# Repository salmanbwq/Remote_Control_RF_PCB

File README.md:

# Remote_Control_RF_PCB
## Decripción
En este repositorio se encuentra el diseño de la placa del Control remoto RF/IR/RFID

Los diseños han sido creador a mano y algunos sacados de https://www.snapeda.com/ y https://4dsystems.com.au/

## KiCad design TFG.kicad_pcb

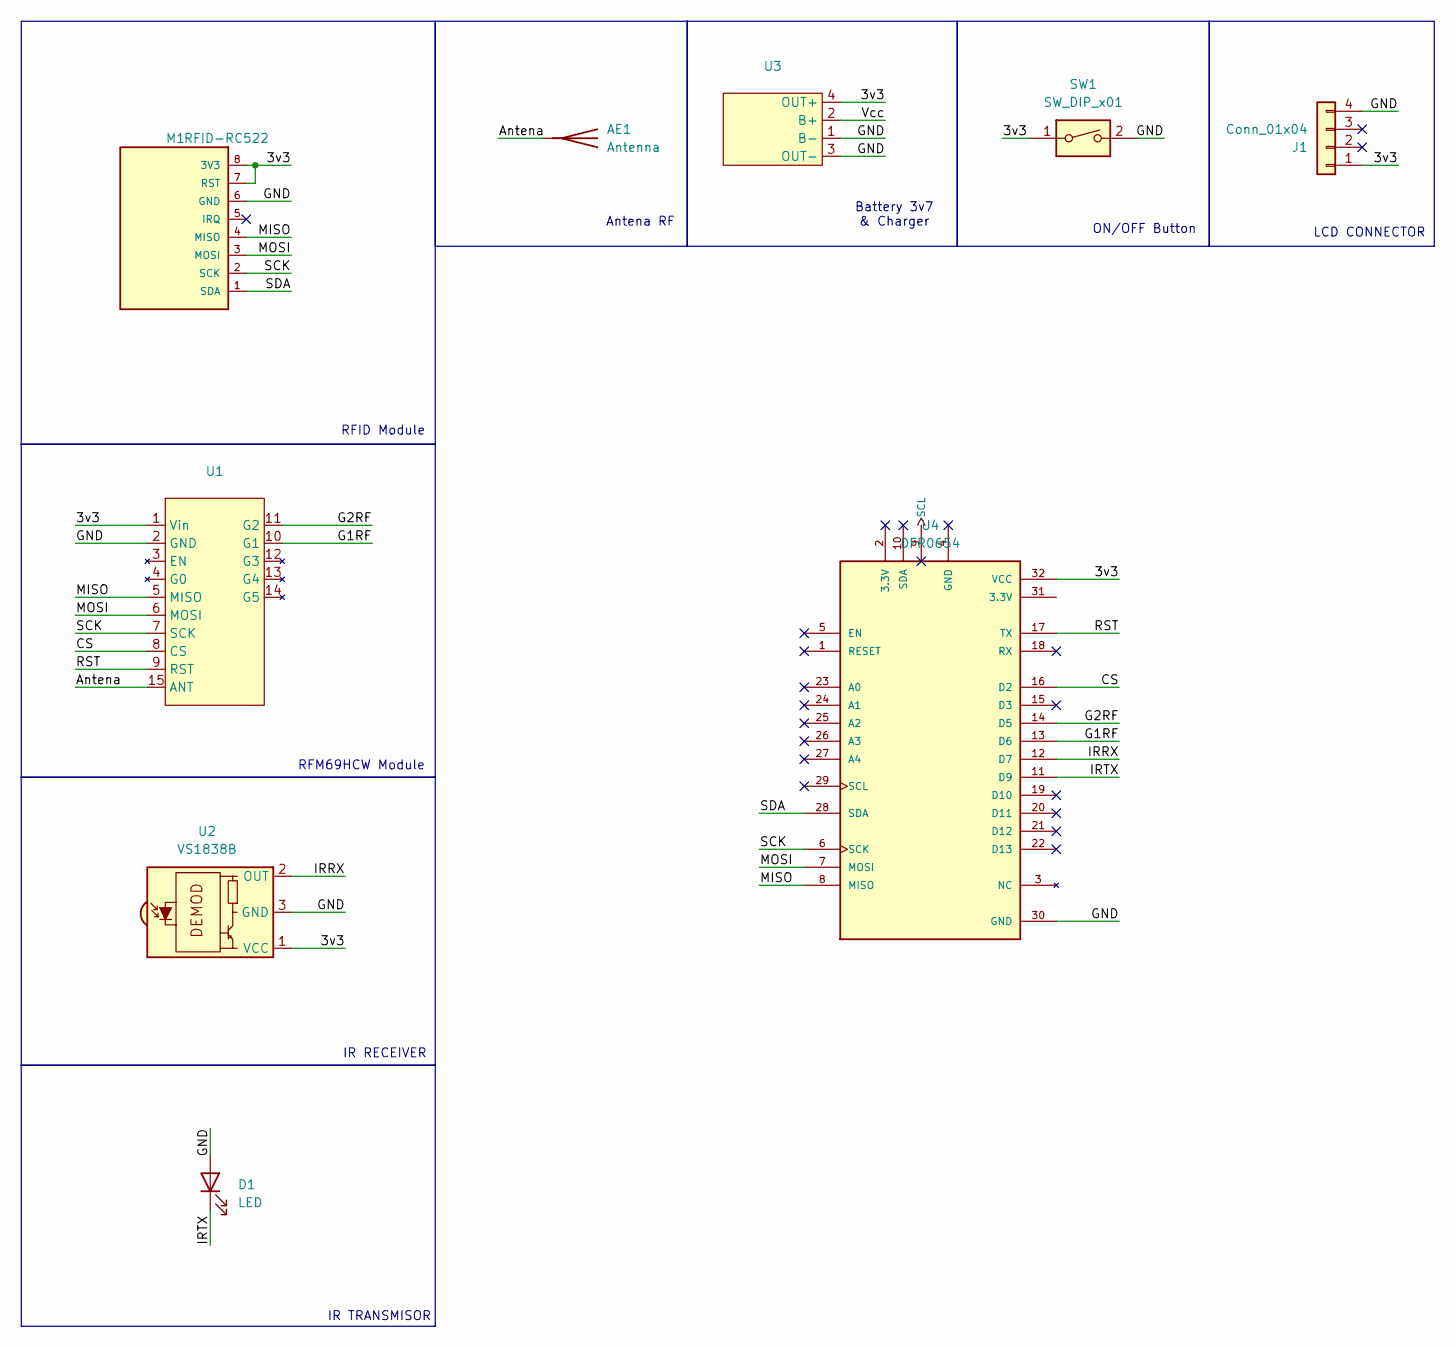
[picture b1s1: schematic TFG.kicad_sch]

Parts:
AE1: Antenna; PinHeader_1x01_P2.54mm_Vertical
D1: LED; LED_D3.0mm_Horizontal_O1.27mm_Z2.0mm_IRBlack
J1: Conn_01x04; JST_EH_B4B-EH-A_1x04_P2.50mm_Vertical
M1: RFID-RC522; MPN RFID-RC522
SW1: SW_DIP_x01; PinSocket_1x02_P2.54mm_Vertical
U1: RF69HCW
U2: VS1838B; Vishay_CAST-3Pin
U3: Battery charger
U4: DFR0654; MODULE_DFR0654

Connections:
/3v3: J1.1, M1.7 (RST), M1.8 (3V3), SW1.1, U1.1 (Vin), U2.1 (VCC), U3.4 (OUT+), U4.32 (VCC)
/Antena: AE1.1 (A), U1.15 (ANT)
/CS: U1.8 (CS), U4.16 (D2)
/G1RF: U1.10 (G1), U4.13 (D6)
/G2RF: U1.11 (G2), U4.14 (D5)
/GND: D1.2 (A), J1.4, M1.6 (GND), SW1.2, U1.2 (GND), U2.3 (GND), U3.1 (B-), U3.3 (OUT-), U4.30 (GND)
/IRRX: U2.2 (OUT), U4.12 (D7)
/IRTX: D1.1 (K), U4.11 (D9)
/MISO: M1.4 (MISO), U1.5 (MISO), U4.8 (MISO)
/MOSI: M1.3 (MOSI), U1.6 (MOSI), U4.7 (MOSI)
/RST: U1.9 (RST), U4.17 (TX)
/SCK: M1.2 (SCK), U1.7 (SCK), U4.6 (SCK)
/SDA: M1.1 (SDA), U4.28 (SDA)
/Vcc: U3.2 (B+)

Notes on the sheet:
IR RECEIVER
RFM69HCW Module
IR TRANSMISOR
RFID Module
LCD CONNECTOR
Antena RF
ON/OFF Button
Battery 3v7 & Charger

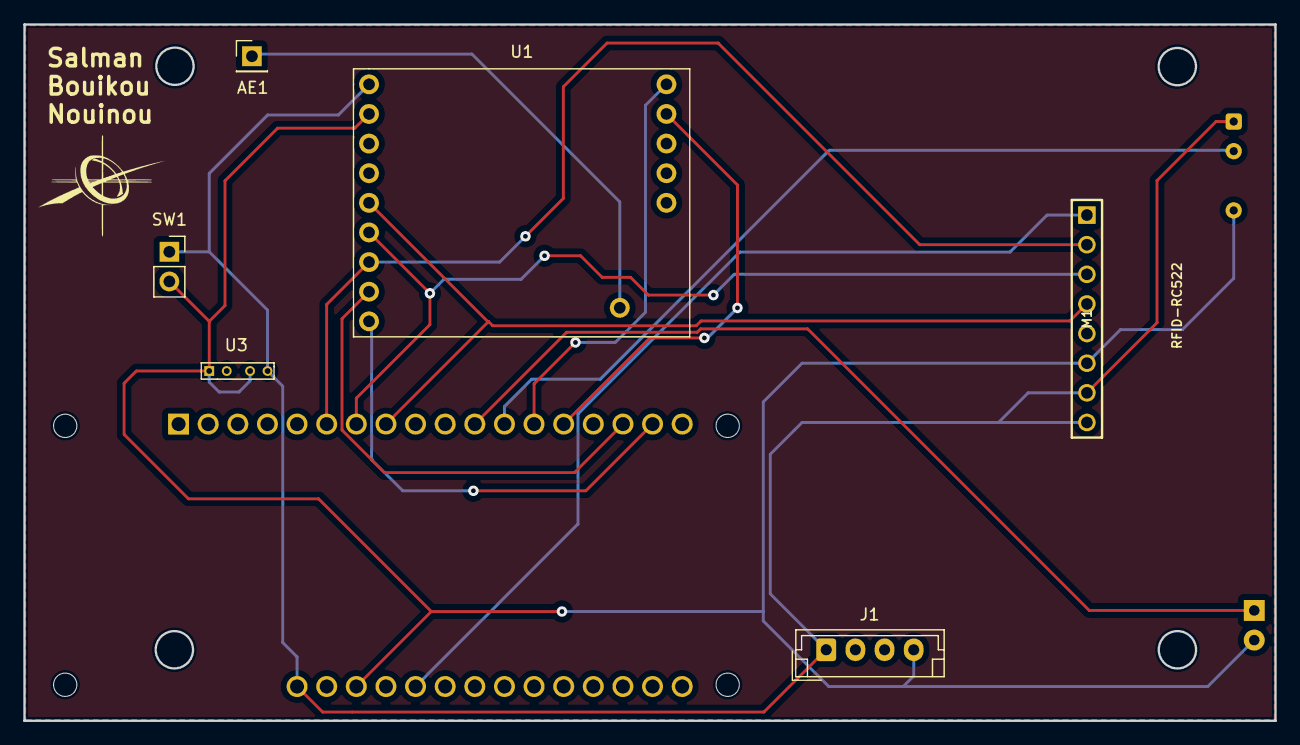
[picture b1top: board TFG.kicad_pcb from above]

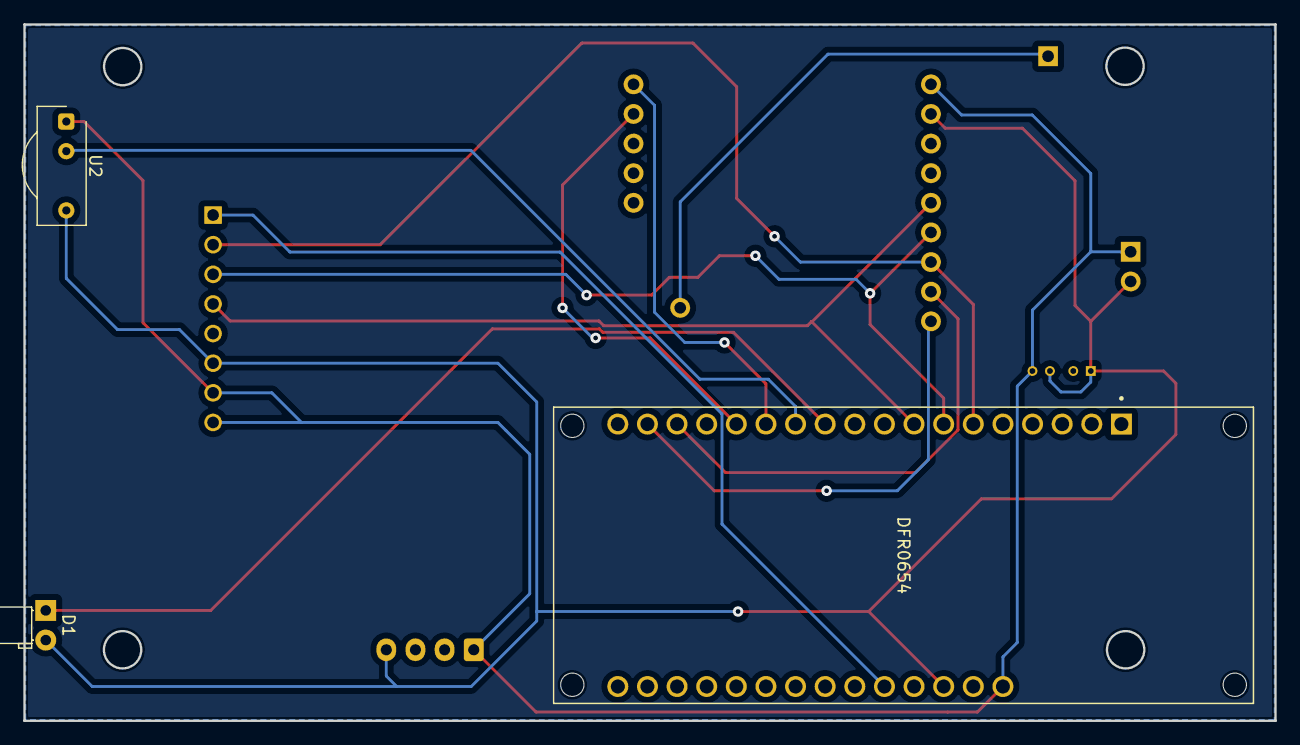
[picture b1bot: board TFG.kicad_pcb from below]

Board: 2 copper layers, 107.3 x 59.7 mm, 9 parts (3 on the bottom side), 13 nets.

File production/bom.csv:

Designator,Footprint,Quantity,Value,LCSC Part #
AE1,PinHeader_1x01_P2.54mm_Vertical,1,Antenna,
D1,LED_D3.0mm_Horizontal_O1.27mm_Z2.0mm_IRBlack,1,LED,
J1,JST_EH_B4B-EH-A_1x04_P2.50mm_Vertical,1,Conn_01x04,
M1,RFID-RC522,1,RFID-RC522,RFID-RC522
SW1,PinSocket_1x02_P2.54mm_Vertical,1,SW_DIP_x01,
U1,RF69HCW,1,~,
U2,Vishay_CAST-3Pin,1,VS1838B,
U3,Battery charger,1,~,
U4,MODULE_DFR0654,1,DFR0654,

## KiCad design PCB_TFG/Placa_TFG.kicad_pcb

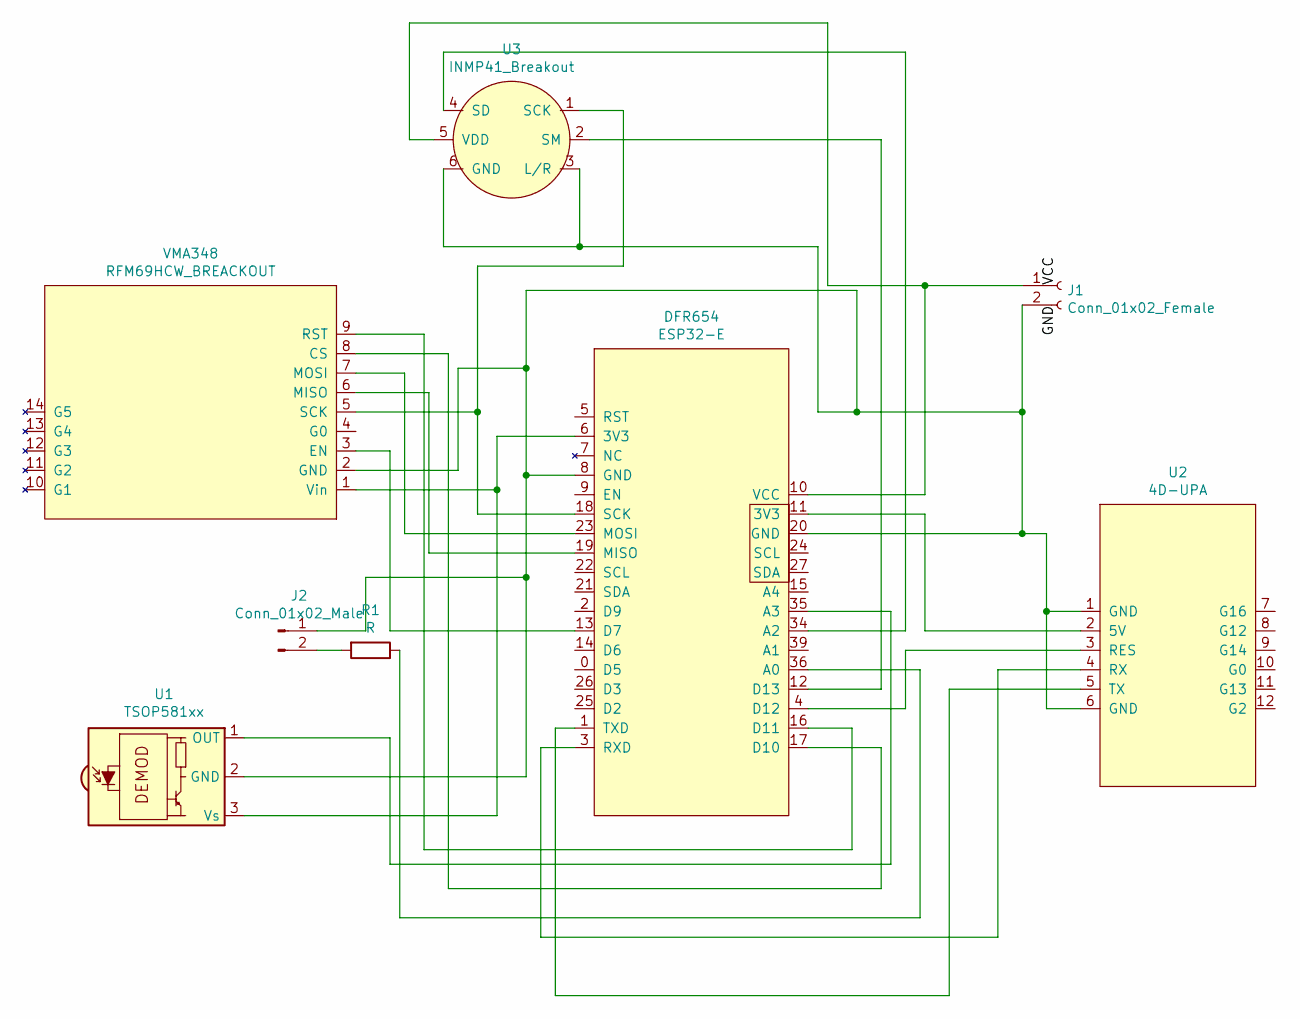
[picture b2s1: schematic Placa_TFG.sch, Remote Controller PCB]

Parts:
DFR654: ESP32-E; MODULE_DFR0654
J1: Conn_01x02_Female; JST_EH_B2B-EH-A_1x02_P2.50mm_Vertical
J2: Conn_01x02_Male; PinSocket_1x02_P2.54mm_Horizontal
R1: R; R_Axial_DIN0204_L3.6mm_D1.6mm_P5.08mm_Horizontal
U1: TSOP581xx; Vishay_MINICAST-3Pin
U2: 4D-UPA
U3: INMP41_Breakout; PinSocket_1x03_P2.54mm_Vertical
VMA348: RFM69HCW_BREACKOUT; PinHeader_1x09_P2.54mm_Vertical

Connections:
unnamed: DFR654.1 (TXD), U2.5 (TX)
unnamed: DFR654.3 (RXD), U2.4 (RX)
unnamed: DFR654.4 (D12), U2.3 (RES)
unnamed: DFR654.6 (3V3), U1.3 (Vs), VMA348.1 (Vin)
unnamed: DFR654.10 (VCC), J1.1, U3.5 (VDD)
unnamed: DFR654.11 (3V3), U2.2 (5V)
unnamed: DFR654.12 (D13), U3.2 (SM)
unnamed: DFR654.13 (D7), VMA348.3 (EN)
unnamed: DFR654.16 (D11), VMA348.9 (RST)
unnamed: DFR654.17 (D10), VMA348.8 (CS)
unnamed: DFR654.18 (SCK), U3.1 (SCK), VMA348.5 (SCK)
unnamed: DFR654.19 (MISO), VMA348.6 (MISO)
unnamed: DFR654.8 (GND), DFR654.20 (GND), J1.2, J2.1, U1.2 (GND), U2.1 (GND), U2.6 (GND), U3.3 (L/R), U3.6 (GND), VMA348.2 (GND)
unnamed: DFR654.23 (MOSI), VMA348.7 (MOSI)
unnamed: DFR654.34 (A2), U3.4 (SD)
unnamed: DFR654.35 (A3), U1.1 (OUT)
unnamed: DFR654.36 (A0), R1.1
unnamed: J2.2, R1.2

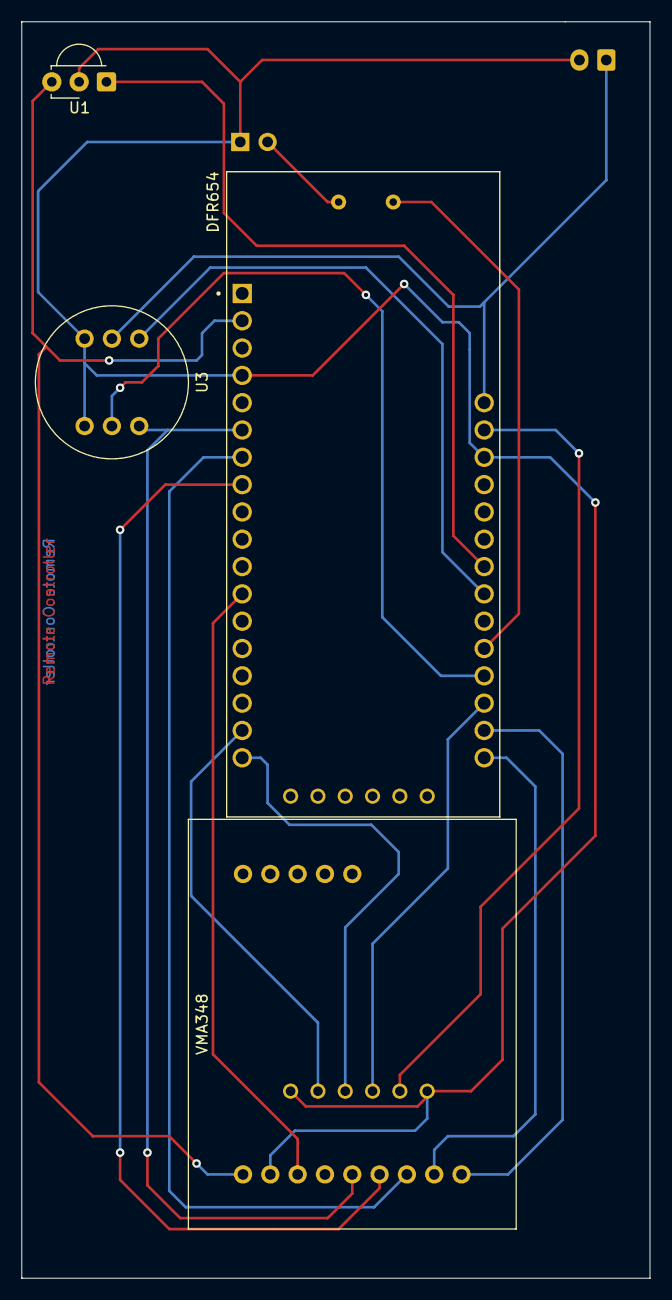
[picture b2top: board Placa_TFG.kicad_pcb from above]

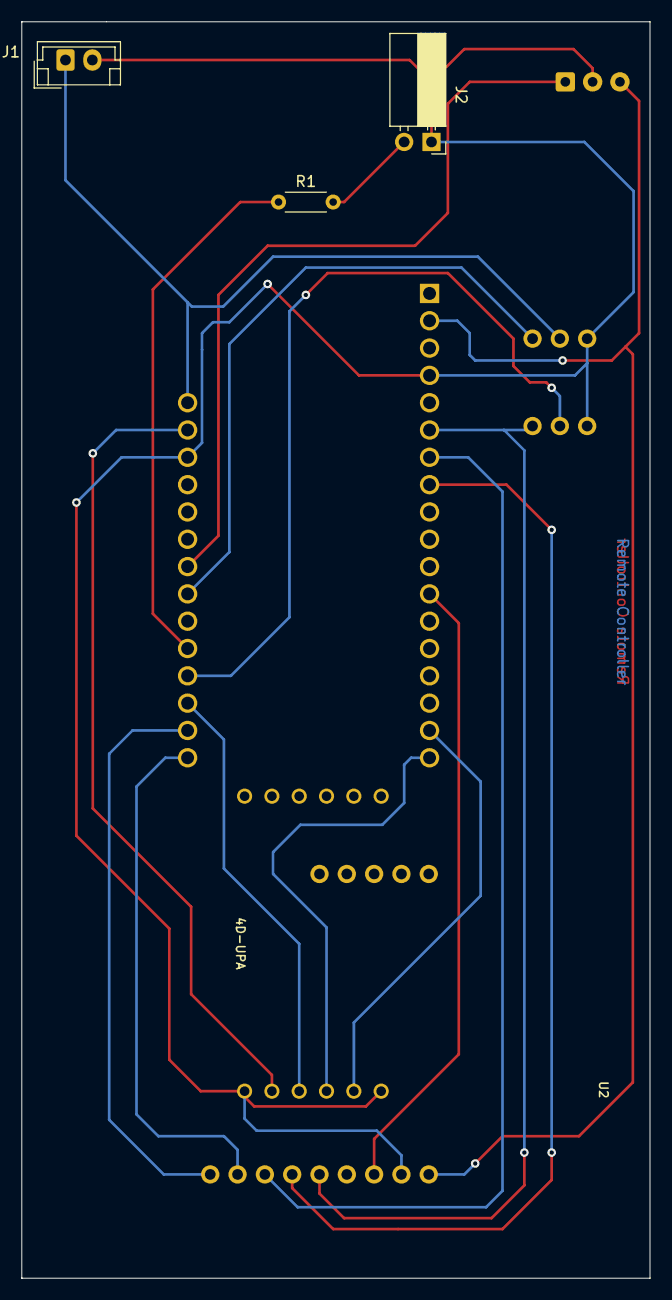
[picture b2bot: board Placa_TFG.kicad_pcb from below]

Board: 2 copper layers, 58.4 x 116.8 mm, 8 parts (4 on the bottom side), 18 nets.

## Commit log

2023-11-27 Versión 0.1
2025-06-21 Uploaded PCB final version
